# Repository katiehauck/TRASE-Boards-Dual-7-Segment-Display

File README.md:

# TRASE-Boards-Dual-7-Segment-Display

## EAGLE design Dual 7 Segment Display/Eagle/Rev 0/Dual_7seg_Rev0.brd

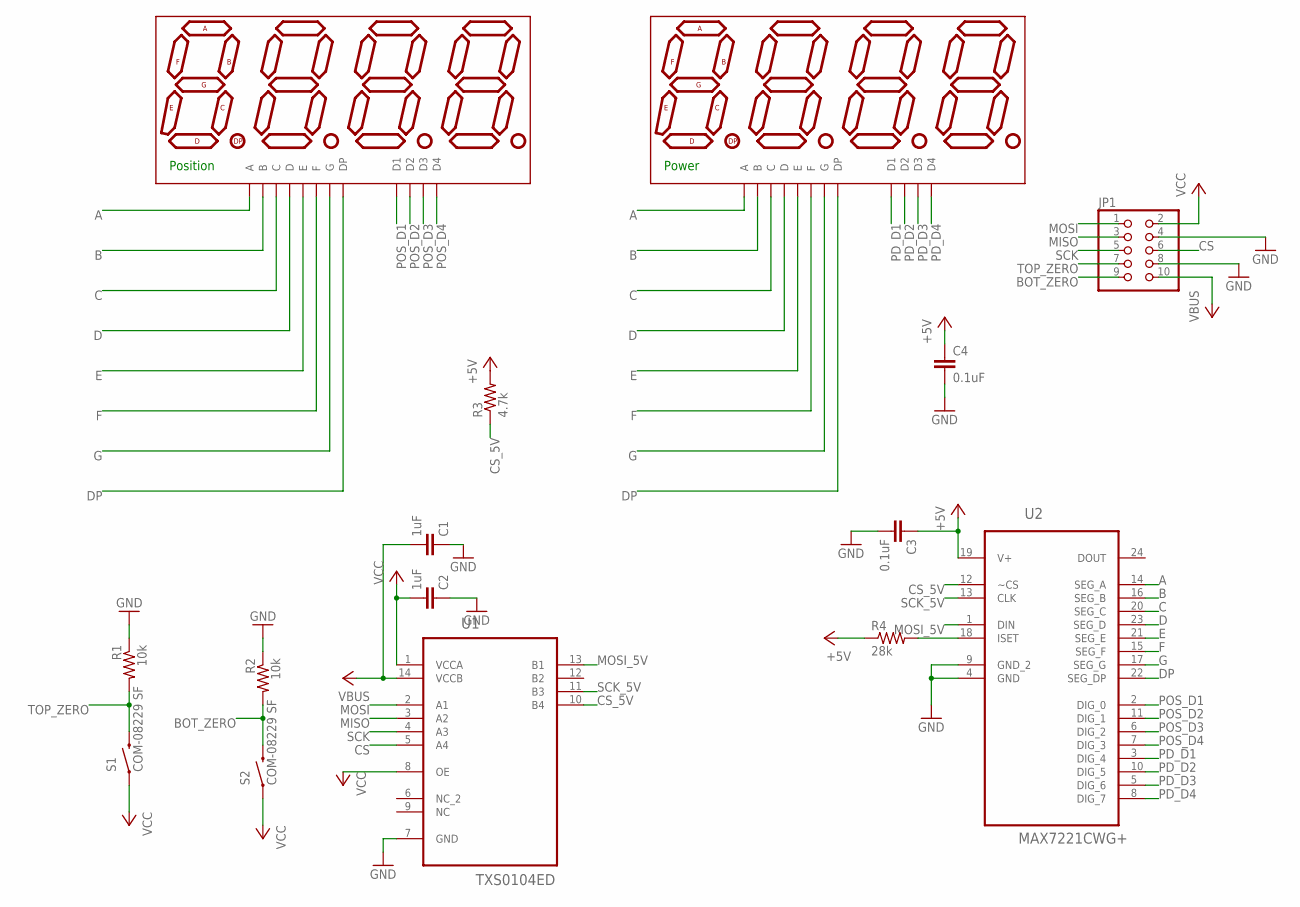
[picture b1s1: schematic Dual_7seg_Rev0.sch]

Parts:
C1, C2: 1uF; C0402
C3, C4: 0.1uF; C0402
DISP1, DISP2: ATA8041AW; 7-SEGMENT-4DIGIT-20MM
JP1: PINHD-2X5; 2X05
R1, R2: 10k; R0402
R3: 4.7k; R0402
R4: 28k; R0402
S1, S2: COM-08229 SF; TACTILE-SWITCH-1101NE
U1: TXS0104ED; SOIC127P600X175-14N
U2: MAX7221CWG+; SOIC127P1032X265-24N

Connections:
+5V: C1.2, C3.1, C4.1, JP1.10, R3.2, R4.1, U1.14 (VCCB), U2.19 (V+)
A: DISP1.11 (A), DISP2.11 (A), U2.14 (SEG_A)
B: DISP1.7 (B), DISP2.7 (B), U2.16 (SEG_B)
BOT_ZERO: JP1.9, R2.2, S2.2
C: DISP1.4 (C), DISP2.4 (C), U2.20 (SEG_C)
CS: JP1.6, U1.5 (A4)
CS_5V: R3.1, U1.10 (B4), U2.12 (~CS)
D: DISP1.2 (D), DISP2.2 (D), U2.23 (SEG_D)
DP: DISP1.3 (DP), DISP2.3 (DP), U2.22 (SEG_DP)
E: DISP1.1 (E), DISP2.1 (E), U2.21 (SEG_E)
F: DISP1.10 (F), DISP2.10 (F), U2.15 (SEG_F)
G: DISP1.5 (G), DISP2.5 (G), U2.17 (SEG_G)
GND: C1.1, C2.1, C3.2, C4.2, JP1.4, JP1.8, R1.1, R2.1, U1.7 (GND), U2.4 (GND), U2.9 (GND_2)
MISO: JP1.3, U1.3 (A2)
MOSI: JP1.1, U1.2 (A1)
MOSI_5V: U1.13 (B1), U2.1 (DIN)
unnamed: R4.2, U2.18 (ISET)
PD_D1: DISP2.12 (D1), U2.3 (DIG_4)
PD_D2: DISP2.9 (D2), U2.10 (DIG_5)
PD_D3: DISP2.8 (D3), U2.5 (DIG_6)
PD_D4: DISP2.6 (D4), U2.8 (DIG_7)
POS_D1: DISP1.12 (D1), U2.2 (DIG_0)
POS_D2: DISP1.9 (D2), U2.11 (DIG_1)
POS_D3: DISP1.8 (D3), U2.6 (DIG_2)
POS_D4: DISP1.6 (D4), U2.7 (DIG_3)
SCK: JP1.5, U1.4 (A3)
SCK_5V: U1.11 (B3), U2.13 (CLK)
TOP_ZERO: JP1.7, R1.2, S1.2
VCC: C2.2, JP1.2, S1.1, S2.1, U1.1 (VCCA), U1.8 (OE)

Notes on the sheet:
Position
Power

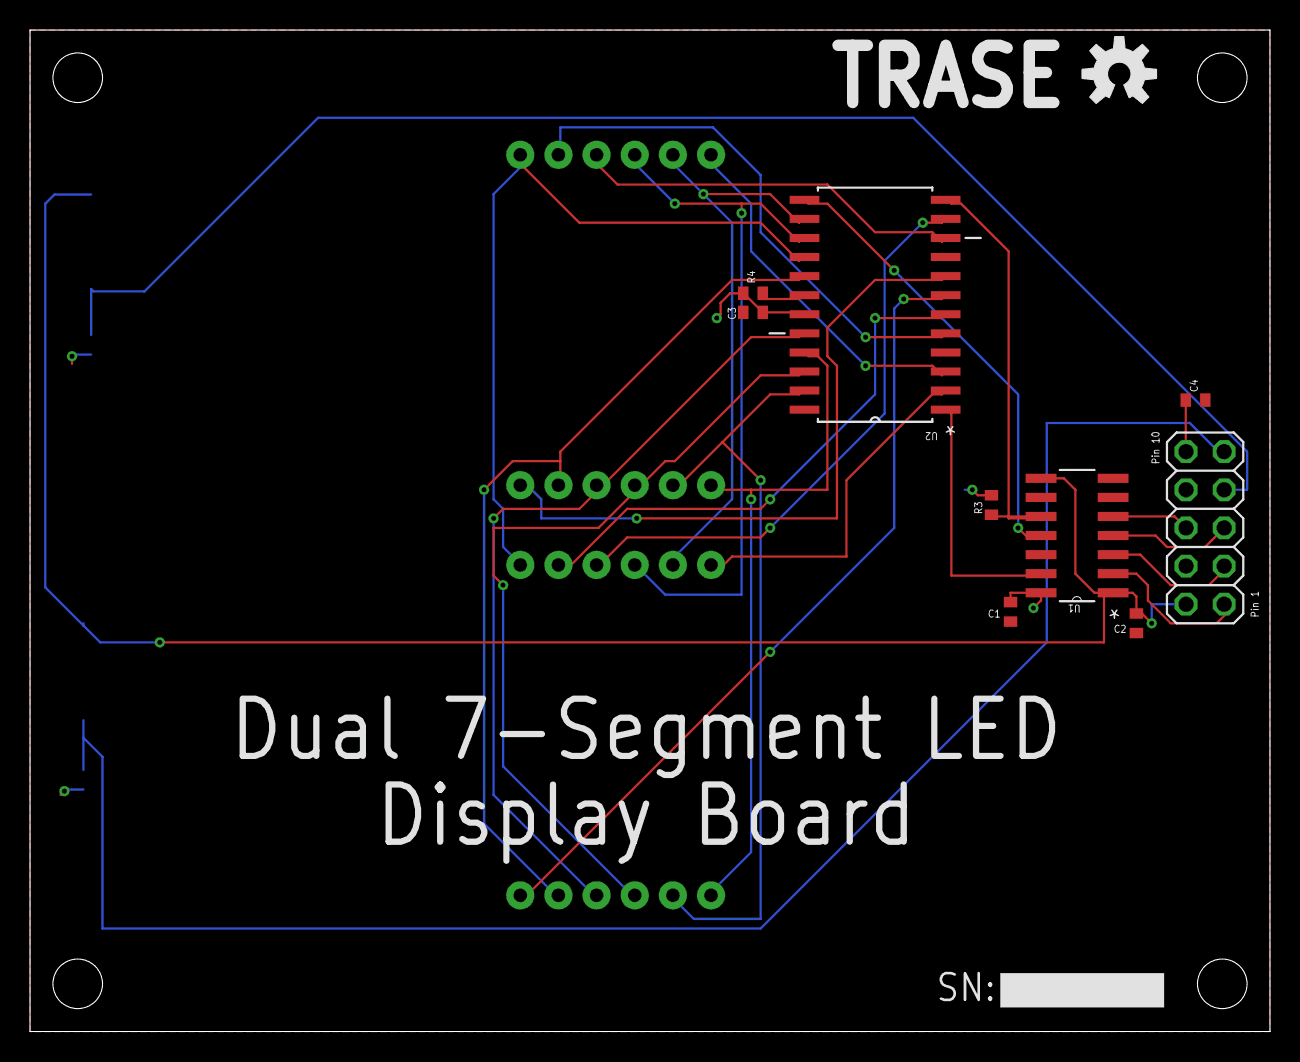
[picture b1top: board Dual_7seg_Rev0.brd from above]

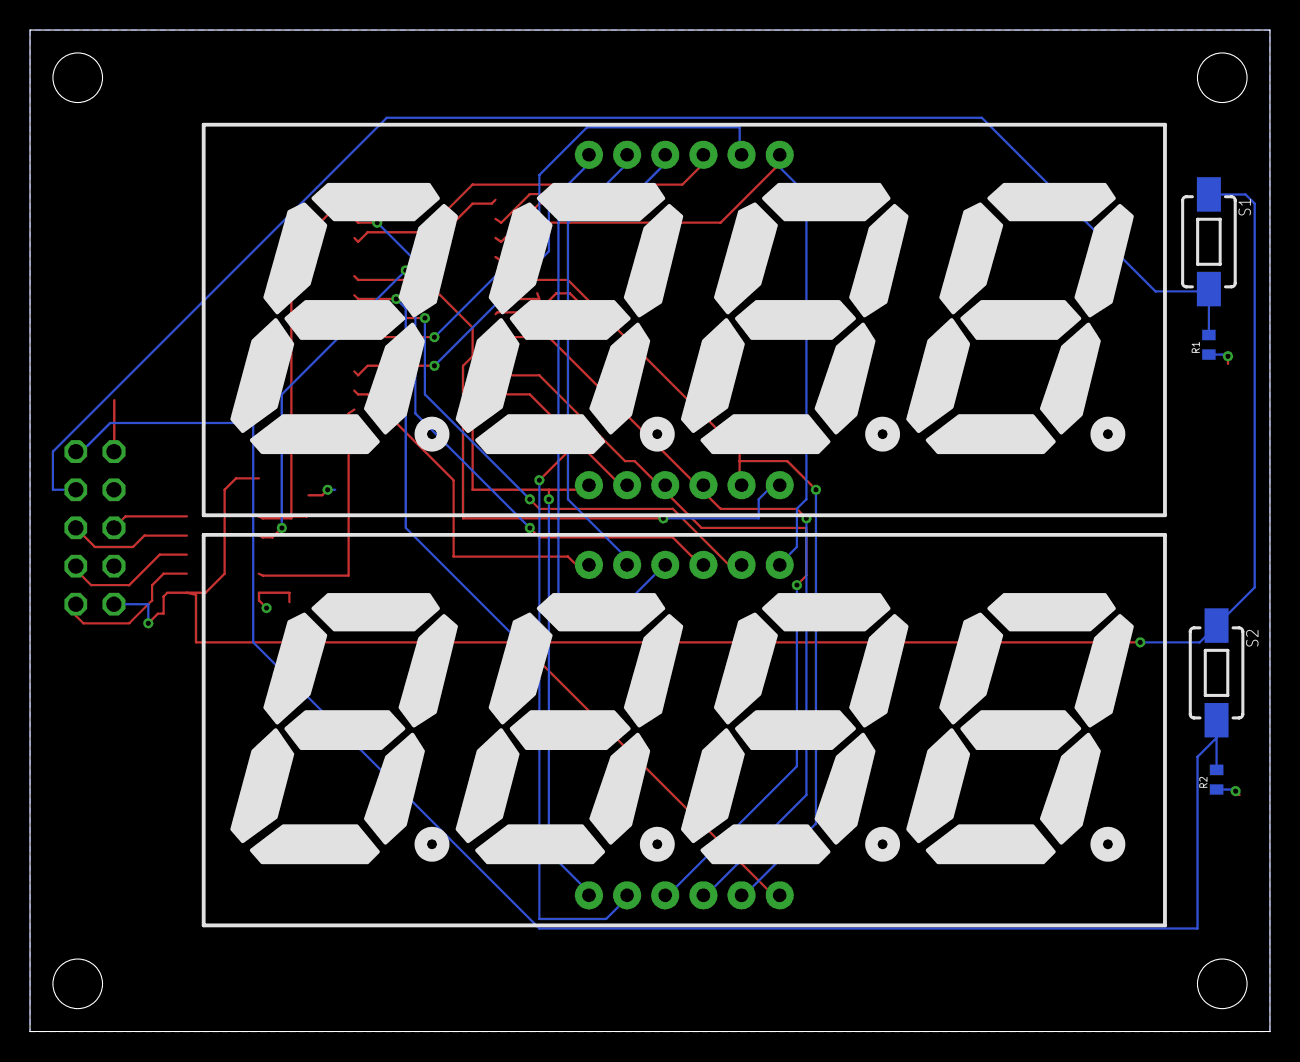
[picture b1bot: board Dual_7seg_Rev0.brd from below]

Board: 2 copper layers, 82.5 x 66.7 mm, 20 parts (6 on the bottom side), 29 nets.

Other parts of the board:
U$1, U$2, U$3, U$5: STAND-OFF
U$4: OSHW-LOGO-M

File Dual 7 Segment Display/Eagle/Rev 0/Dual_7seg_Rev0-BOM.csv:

"Qty","Value","Device","Package","Parts","Description"
"2","1uF","C-EUC0402","C0402","C1, C2","CAPACITOR, European symbol"
"2","0.1uF","C-EUC0402","C0402","C3, C4","CAPACITOR, European symbol"
"2","ATA8041AW","7-SEGMENT-4DIGIT-20MM-WHITE","7-SEGMENT-4DIGIT-20MM","DISP1, DISP2","4 Digit 7 Segment Display"
"1","","PINHD-2X5","2X05","JP1","PIN HEADER"
"2","10k","R-US_R0402","R0402","R1, R2","RESISTOR, American symbol"
"1","4.7k","R-US_R0402","R0402","R3","RESISTOR, American symbol"
"1","28k","R-US_R0402","R0402","R4","RESISTOR, American symbol"
"2","COM-08229 SF","SWITCH-MOMENTARY-2SMD-1101NE","TACTILE-SWITCH-1101NE","S1, S2","Various NO switches- pushbuttons, reed, etc"
"1","TXS0104ED","TXS0104ED","SOIC127P600X175-14N","U1","4-BIT BIDIRECTIONAL VOLTAGE-LEVEL TRANSLATOR  FOR OPEN-DRAIN AND PUSH-PULL APPLICATIONS"
"1","MAX7221CWG+","MAX7221CWG+","SOIC127P1032X265-24N","U2","Serially Interfaced, 8-Digit LED Display Drivers"

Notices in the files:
parts and their libraries:
SparkFun-LED: Licensing: Creative Commons ShareAlike 4.0 International - https://creativecommons.org/licenses/by-sa/4.0
